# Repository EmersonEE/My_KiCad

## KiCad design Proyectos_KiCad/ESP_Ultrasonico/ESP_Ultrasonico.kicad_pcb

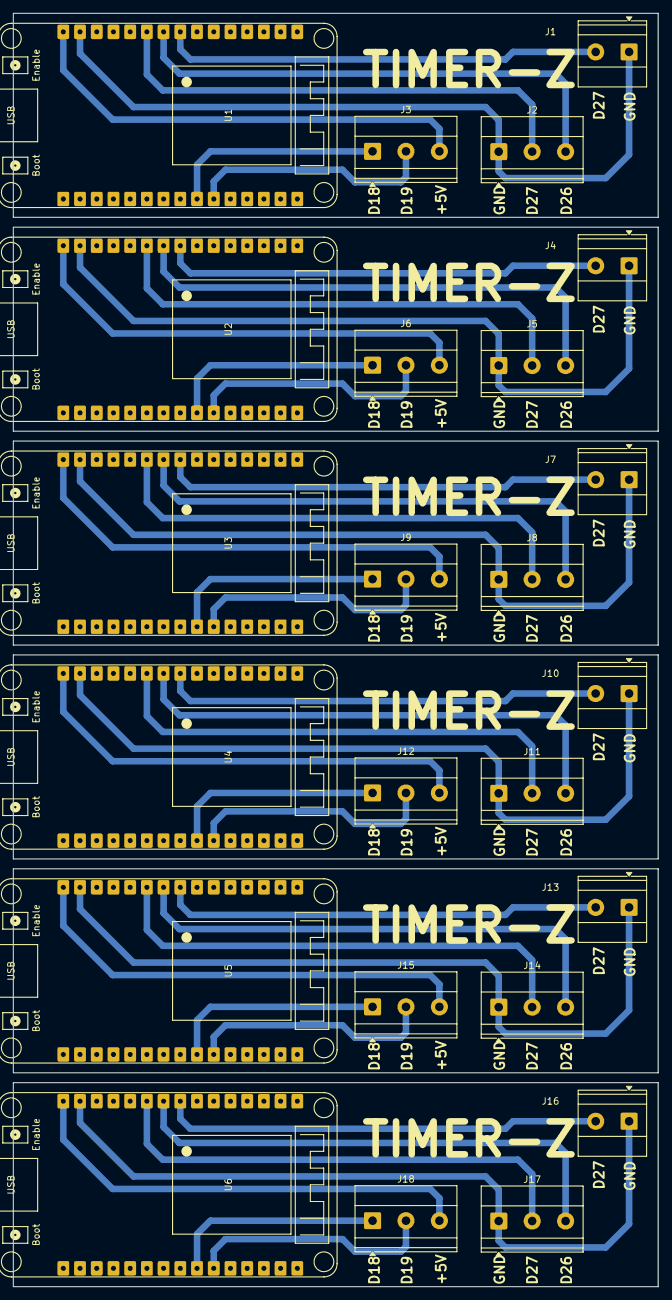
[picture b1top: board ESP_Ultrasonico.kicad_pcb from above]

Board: 2 copper layers, 98.0 x 193.5 mm, 24 parts (0 on the bottom side), 7 nets.

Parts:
J1, J4, J7, J10, J13, J16: Screw_Terminal_01x02; TerminalBlock_Phoenix_MKDS-1,5-2-5.08_1x02_P5.08mm_Horizont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
J2, J3, J5, J6, J8, J9, J11, J12, J14, J15, J17, J18: Screw_Terminal_01x03; TerminalBlock_Phoenix_MKDS-1,5-3-5.08_1x03_P5.08mm_Horizont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
U1, U2, U3, U4, U5, U6: ESP32_DevKit_V1_DOIT; ESP32_DEVKIT_V1_E32

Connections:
5V: J3.3, J6.3, J9.3, J12.3, J15.3, J18.3, U1.15 (VIN), U2.15 (VIN), U3.15 (VIN), U4.15 (VIN), U5.15 (VIN), U6.15 (VIN)
/CLK/GPIO18/D18: J3.1, J6.1, J9.1, J12.1, J15.1, J18.1, U1.24 (CLK/GPIO18/D18), U2.24 (CLK/GPIO18/D18), U3.24 (CLK/GPIO18/D18), U4.24 (CLK/GPIO18/D18), U5.24 (CLK/GPIO18/D18), U6.24 (CLK/GPIO18/D18)
/D25/GPIO25/ADC2/DAC1: J1.2, J4.2, J7.2, J10.2, J13.2, J16.2, U1.8 (D25/GPIO25/ADC2/DAC1), U2.8 (D25/GPIO25/ADC2/DAC1), U3.8 (D25/GPIO25/ADC2/DAC1), U4.8 (D25/GPIO25/ADC2/DAC1), U5.8 (D25/GPIO25/ADC2/DAC1), U6.8 (D25/GPIO25/ADC2/DAC1)
/D26/GPIO26/ADC2/DAC2: J2.3, J5.3, J8.3, J11.3, J14.3, J17.3, U1.9 (D26/GPIO26/ADC2/DAC2), U2.9 (D26/GPIO26/ADC2/DAC2), U3.9 (D26/GPIO26/ADC2/DAC2), U4.9 (D26/GPIO26/ADC2/DAC2), U5.9 (D26/GPIO26/ADC2/DAC2), U6.9 (D26/GPIO26/ADC2/DAC2)
/D27/GPIO27/ADC2/TOUCH7: J2.2, J5.2, J8.2, J11.2, J14.2, J17.2, U1.10 (D27/GPIO27/ADC2/TOUCH7), U2.10 (D27/GPIO27/ADC2/TOUCH7), U3.10 (D27/GPIO27/ADC2/TOUCH7), U4.10 (D27/GPIO27/ADC2/TOUCH7), U5.10 (D27/GPIO27/ADC2/TOUCH7), U6.10 (D27/GPIO27/ADC2/TOUCH7)
/MISO/GPIO19/D19: J3.2, J6.2, J9.2, J12.2, J15.2, J18.2, U1.25 (MISO/GPIO19/D19), U2.25 (MISO/GPIO19/D19), U3.25 (MISO/GPIO19/D19), U4.25 (MISO/GPIO19/D19), U5.25 (MISO/GPIO19/D19), U6.25 (MISO/GPIO19/D19)
GND: J1.1, J2.1, J4.1, J5.1, J7.1, J8.1, J10.1, J11.1, J13.1, J14.1, J16.1, J17.1, U1.14 (GND), U2.14 (GND), U3.14 (GND), U4.14 (GND), U5.14 (GND), U6.14 (GND)

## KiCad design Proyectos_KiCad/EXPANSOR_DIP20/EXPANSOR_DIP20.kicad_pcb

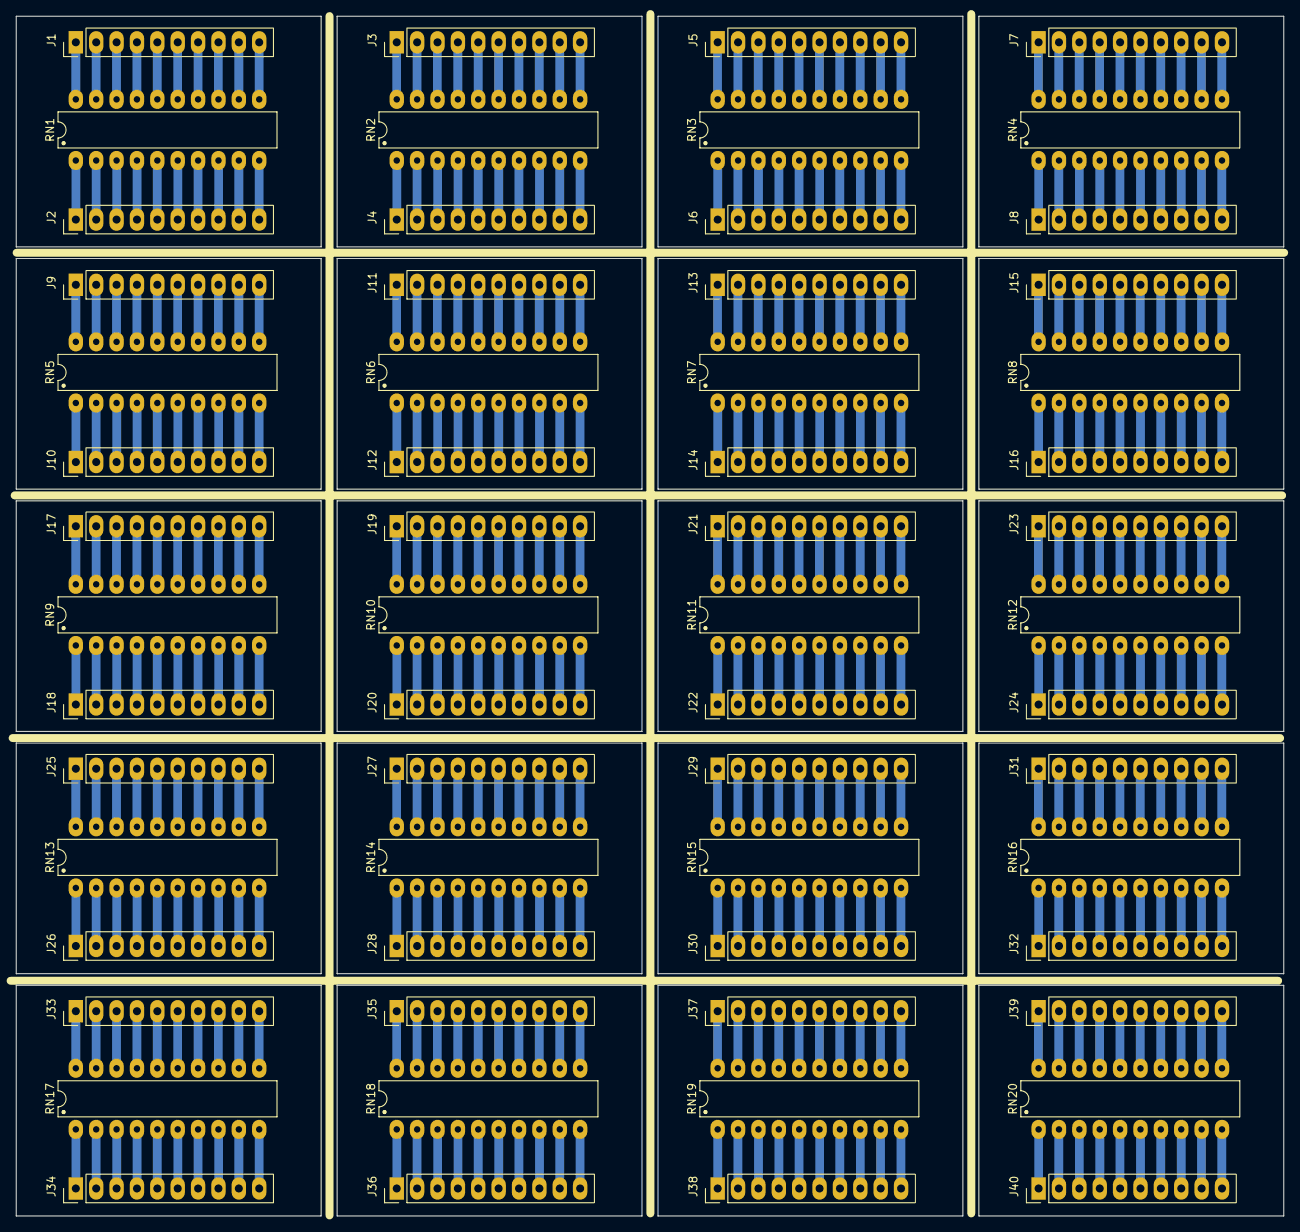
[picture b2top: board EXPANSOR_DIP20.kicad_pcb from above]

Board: 2 copper layers, 158.0 x 149.5 mm, 60 parts (0 on the bottom side), 20 nets.

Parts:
J1, J2, J3, J4, J5, J6, J7, J8, J9, J10, J11, J12, J13, J14, J15, J16, J17, J18, J19, J20, J21, J22, J23, J24, J25, J26, J27, J28, J29, J30, J31, J32, J33, J34, J35, J36, J37, J38, J39, J40: Conn_01x10; PinHeader_1x10_P2.54mm_Vertical
RN1, RN2, RN3, RN4, RN5, RN6, RN7, RN8, RN9, RN10, RN11, RN12, RN13, RN14, RN15, RN16, RN17, RN18, RN19, RN20: R_Pack_DIP-20; DIP-20_W7.62mm_LongPads

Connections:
unnamed: J1.1, J3.1, J5.1, J7.1, J9.1, J11.1, J13.1, J15.1, J17.1, J19.1, J21.1, J23.1, J25.1, J27.1, J29.1, J31.1, J33.1, J35.1, J37.1, J39.1, RN1.20 (R1.2), RN2.20 (R1.2), RN3.20 (R1.2), RN4.20 (R1.2), RN5.20 (R1.2), RN6.20 (R1.2), RN7.20 (R1.2), RN8.20 (R1.2), RN9.20 (R1.2), RN10.20 (R1.2), RN11.20 (R1.2), RN12.20 (R1.2), RN13.20 (R1.2), RN14.20 (R1.2), RN15.20 (R1.2), RN16.20 (R1.2), RN17.20 (R1.2), RN18.20 (R1.2), RN19.20 (R1.2), RN20.20 (R1.2)
unnamed: J1.2, J3.2, J5.2, J7.2, J9.2, J11.2, J13.2, J15.2, J17.2, J19.2, J21.2, J23.2, J25.2, J27.2, J29.2, J31.2, J33.2, J35.2, J37.2, J39.2, RN1.19 (R2.2), RN2.19 (R2.2), RN3.19 (R2.2), RN4.19 (R2.2), RN5.19 (R2.2), RN6.19 (R2.2), RN7.19 (R2.2), RN8.19 (R2.2), RN9.19 (R2.2), RN10.19 (R2.2), RN11.19 (R2.2), RN12.19 (R2.2), RN13.19 (R2.2), RN14.19 (R2.2), RN15.19 (R2.2), RN16.19 (R2.2), RN17.19 (R2.2), RN18.19 (R2.2), RN19.19 (R2.2), RN20.19 (R2.2)
unnamed: J1.3, J3.3, J5.3, J7.3, J9.3, J11.3, J13.3, J15.3, J17.3, J19.3, J21.3, J23.3, J25.3, J27.3, J29.3, J31.3, J33.3, J35.3, J37.3, J39.3, RN1.18 (R3.2), RN2.18 (R3.2), RN3.18 (R3.2), RN4.18 (R3.2), RN5.18 (R3.2), RN6.18 (R3.2), RN7.18 (R3.2), RN8.18 (R3.2), RN9.18 (R3.2), RN10.18 (R3.2), RN11.18 (R3.2), RN12.18 (R3.2), RN13.18 (R3.2), RN14.18 (R3.2), RN15.18 (R3.2), RN16.18 (R3.2), RN17.18 (R3.2), RN18.18 (R3.2), RN19.18 (R3.2), RN20.18 (R3.2)
unnamed: J1.4, J3.4, J5.4, J7.4, J9.4, J11.4, J13.4, J15.4, J17.4, J19.4, J21.4, J23.4, J25.4, J27.4, J29.4, J31.4, J33.4, J35.4, J37.4, J39.4, RN1.17 (R4.2), RN2.17 (R4.2), RN3.17 (R4.2), RN4.17 (R4.2), RN5.17 (R4.2), RN6.17 (R4.2), RN7.17 (R4.2), RN8.17 (R4.2), RN9.17 (R4.2), RN10.17 (R4.2), RN11.17 (R4.2), RN12.17 (R4.2), RN13.17 (R4.2), RN14.17 (R4.2), RN15.17 (R4.2), RN16.17 (R4.2), RN17.17 (R4.2), RN18.17 (R4.2), RN19.17 (R4.2), RN20.17 (R4.2)
unnamed: J1.5, J3.5, J5.5, J7.5, J9.5, J11.5, J13.5, J15.5, J17.5, J19.5, J21.5, J23.5, J25.5, J27.5, J29.5, J31.5, J33.5, J35.5, J37.5, J39.5, RN1.16 (R5.2), RN2.16 (R5.2), RN3.16 (R5.2), RN4.16 (R5.2), RN5.16 (R5.2), RN6.16 (R5.2), RN7.16 (R5.2), RN8.16 (R5.2), RN9.16 (R5.2), RN10.16 (R5.2), RN11.16 (R5.2), RN12.16 (R5.2), RN13.16 (R5.2), RN14.16 (R5.2), RN15.16 (R5.2), RN16.16 (R5.2), RN17.16 (R5.2), RN18.16 (R5.2), RN19.16 (R5.2), RN20.16 (R5.2)
unnamed: J1.6, J3.6, J5.6, J7.6, J9.6, J11.6, J13.6, J15.6, J17.6, J19.6, J21.6, J23.6, J25.6, J27.6, J29.6, J31.6, J33.6, J35.6, J37.6, J39.6, RN1.15 (R6.2), RN2.15 (R6.2), RN3.15 (R6.2), RN4.15 (R6.2), RN5.15 (R6.2), RN6.15 (R6.2), RN7.15 (R6.2), RN8.15 (R6.2), RN9.15 (R6.2), RN10.15 (R6.2), RN11.15 (R6.2), RN12.15 (R6.2), RN13.15 (R6.2), RN14.15 (R6.2), RN15.15 (R6.2), RN16.15 (R6.2), RN17.15 (R6.2), RN18.15 (R6.2), RN19.15 (R6.2), RN20.15 (R6.2)
unnamed: J1.7, J3.7, J5.7, J7.7, J9.7, J11.7, J13.7, J15.7, J17.7, J19.7, J21.7, J23.7, J25.7, J27.7, J29.7, J31.7, J33.7, J35.7, J37.7, J39.7, RN1.14 (R7.2), RN2.14 (R7.2), RN3.14 (R7.2), RN4.14 (R7.2), RN5.14 (R7.2), RN6.14 (R7.2), RN7.14 (R7.2), RN8.14 (R7.2), RN9.14 (R7.2), RN10.14 (R7.2), RN11.14 (R7.2), RN12.14 (R7.2), RN13.14 (R7.2), RN14.14 (R7.2), RN15.14 (R7.2), RN16.14 (R7.2), RN17.14 (R7.2), RN18.14 (R7.2), RN19.14 (R7.2), RN20.14 (R7.2)
unnamed: J1.8, J3.8, J5.8, J7.8, J9.8, J11.8, J13.8, J15.8, J17.8, J19.8, J21.8, J23.8, J25.8, J27.8, J29.8, J31.8, J33.8, J35.8, J37.8, J39.8, RN1.13 (R8.2), RN2.13 (R8.2), RN3.13 (R8.2), RN4.13 (R8.2), RN5.13 (R8.2), RN6.13 (R8.2), RN7.13 (R8.2), RN8.13 (R8.2), RN9.13 (R8.2), RN10.13 (R8.2), RN11.13 (R8.2), RN12.13 (R8.2), RN13.13 (R8.2), RN14.13 (R8.2), RN15.13 (R8.2), RN16.13 (R8.2), RN17.13 (R8.2), RN18.13 (R8.2), RN19.13 (R8.2), RN20.13 (R8.2)
unnamed: J1.9, J3.9, J5.9, J7.9, J9.9, J11.9, J13.9, J15.9, J17.9, J19.9, J21.9, J23.9, J25.9, J27.9, J29.9, J31.9, J33.9, J35.9, J37.9, J39.9, RN1.12 (R9.2), RN2.12 (R9.2), RN3.12 (R9.2), RN4.12 (R9.2), RN5.12 (R9.2), RN6.12 (R9.2), RN7.12 (R9.2), RN8.12 (R9.2), RN9.12 (R9.2), RN10.12 (R9.2), RN11.12 (R9.2), RN12.12 (R9.2), RN13.12 (R9.2), RN14.12 (R9.2), RN15.12 (R9.2), RN16.12 (R9.2), RN17.12 (R9.2), RN18.12 (R9.2), RN19.12 (R9.2), RN20.12 (R9.2)
unnamed: J1.10, J3.10, J5.10, J7.10, J9.10, J11.10, J13.10, J15.10, J17.10, J19.10, J21.10, J23.10, J25.10, J27.10, J29.10, J31.10, J33.10, J35.10, J37.10, J39.10, RN1.11 (R10.2), RN2.11 (R10.2), RN3.11 (R10.2), RN4.11 (R10.2), RN5.11 (R10.2), RN6.11 (R10.2), RN7.11 (R10.2), RN8.11 (R10.2), RN9.11 (R10.2), RN10.11 (R10.2), RN11.11 (R10.2), RN12.11 (R10.2), RN13.11 (R10.2), RN14.11 (R10.2), RN15.11 (R10.2), RN16.11 (R10.2), RN17.11 (R10.2), RN18.11 (R10.2), RN19.11 (R10.2), RN20.11 (R10.2)
unnamed: J2.1, J4.1, J6.1, J8.1, J10.1, J12.1, J14.1, J16.1, J18.1, J20.1, J22.1, J24.1, J26.1, J28.1, J30.1, J32.1, J34.1, J36.1, J38.1, J40.1, RN1.1 (R1.1), RN2.1 (R1.1), RN3.1 (R1.1), RN4.1 (R1.1), RN5.1 (R1.1), RN6.1 (R1.1), RN7.1 (R1.1), RN8.1 (R1.1), RN9.1 (R1.1), RN10.1 (R1.1), RN11.1 (R1.1), RN12.1 (R1.1), RN13.1 (R1.1), RN14.1 (R1.1), RN15.1 (R1.1), RN16.1 (R1.1), RN17.1 (R1.1), RN18.1 (R1.1), RN19.1 (R1.1), RN20.1 (R1.1)
unnamed: J2.2, J4.2, J6.2, J8.2, J10.2, J12.2, J14.2, J16.2, J18.2, J20.2, J22.2, J24.2, J26.2, J28.2, J30.2, J32.2, J34.2, J36.2, J38.2, J40.2, RN1.2 (R2.1), RN2.2 (R2.1), RN3.2 (R2.1), RN4.2 (R2.1), RN5.2 (R2.1), RN6.2 (R2.1), RN7.2 (R2.1), RN8.2 (R2.1), RN9.2 (R2.1), RN10.2 (R2.1), RN11.2 (R2.1), RN12.2 (R2.1), RN13.2 (R2.1), RN14.2 (R2.1), RN15.2 (R2.1), RN16.2 (R2.1), RN17.2 (R2.1), RN18.2 (R2.1), RN19.2 (R2.1), RN20.2 (R2.1)
unnamed: J2.3, J4.3, J6.3, J8.3, J10.3, J12.3, J14.3, J16.3, J18.3, J20.3, J22.3, J24.3, J26.3, J28.3, J30.3, J32.3, J34.3, J36.3, J38.3, J40.3, RN1.3 (R3.1), RN2.3 (R3.1), RN3.3 (R3.1), RN4.3 (R3.1), RN5.3 (R3.1), RN6.3 (R3.1), RN7.3 (R3.1), RN8.3 (R3.1), RN9.3 (R3.1), RN10.3 (R3.1), RN11.3 (R3.1), RN12.3 (R3.1), RN13.3 (R3.1), RN14.3 (R3.1), RN15.3 (R3.1), RN16.3 (R3.1), RN17.3 (R3.1), RN18.3 (R3.1), RN19.3 (R3.1), RN20.3 (R3.1)
unnamed: J2.4, J4.4, J6.4, J8.4, J10.4, J12.4, J14.4, J16.4, J18.4, J20.4, J22.4, J24.4, J26.4, J28.4, J30.4, J32.4, J34.4, J36.4, J38.4, J40.4, RN1.4 (R4.1), RN2.4 (R4.1), RN3.4 (R4.1), RN4.4 (R4.1), RN5.4 (R4.1), RN6.4 (R4.1), RN7.4 (R4.1), RN8.4 (R4.1), RN9.4 (R4.1), RN10.4 (R4.1), RN11.4 (R4.1), RN12.4 (R4.1), RN13.4 (R4.1), RN14.4 (R4.1), RN15.4 (R4.1), RN16.4 (R4.1), RN17.4 (R4.1), RN18.4 (R4.1), RN19.4 (R4.1), RN20.4 (R4.1)
unnamed: J2.5, J4.5, J6.5, J8.5, J10.5, J12.5, J14.5, J16.5, J18.5, J20.5, J22.5, J24.5, J26.5, J28.5, J30.5, J32.5, J34.5, J36.5, J38.5, J40.5, RN1.5 (R5.1), RN2.5 (R5.1), RN3.5 (R5.1), RN4.5 (R5.1), RN5.5 (R5.1), RN6.5 (R5.1), RN7.5 (R5.1), RN8.5 (R5.1), RN9.5 (R5.1), RN10.5 (R5.1), RN11.5 (R5.1), RN12.5 (R5.1), RN13.5 (R5.1), RN14.5 (R5.1), RN15.5 (R5.1), RN16.5 (R5.1), RN17.5 (R5.1), RN18.5 (R5.1), RN19.5 (R5.1), RN20.5 (R5.1)
unnamed: J2.6, J4.6, J6.6, J8.6, J10.6, J12.6, J14.6, J16.6, J18.6, J20.6, J22.6, J24.6, J26.6, J28.6, J30.6, J32.6, J34.6, J36.6, J38.6, J40.6, RN1.6 (R6.1), RN2.6 (R6.1), RN3.6 (R6.1), RN4.6 (R6.1), RN5.6 (R6.1), RN6.6 (R6.1), RN7.6 (R6.1), RN8.6 (R6.1), RN9.6 (R6.1), RN10.6 (R6.1), RN11.6 (R6.1), RN12.6 (R6.1), RN13.6 (R6.1), RN14.6 (R6.1), RN15.6 (R6.1), RN16.6 (R6.1), RN17.6 (R6.1), RN18.6 (R6.1), RN19.6 (R6.1), RN20.6 (R6.1)
unnamed: J2.7, J4.7, J6.7, J8.7, J10.7, J12.7, J14.7, J16.7, J18.7, J20.7, J22.7, J24.7, J26.7, J28.7, J30.7, J32.7, J34.7, J36.7, J38.7, J40.7, RN1.7 (R7.1), RN2.7 (R7.1), RN3.7 (R7.1), RN4.7 (R7.1), RN5.7 (R7.1), RN6.7 (R7.1), RN7.7 (R7.1), RN8.7 (R7.1), RN9.7 (R7.1), RN10.7 (R7.1), RN11.7 (R7.1), RN12.7 (R7.1), RN13.7 (R7.1), RN14.7 (R7.1), RN15.7 (R7.1), RN16.7 (R7.1), RN17.7 (R7.1), RN18.7 (R7.1), RN19.7 (R7.1), RN20.7 (R7.1)
unnamed: J2.8, J4.8, J6.8, J8.8, J10.8, J12.8, J14.8, J16.8, J18.8, J20.8, J22.8, J24.8, J26.8, J28.8, J30.8, J32.8, J34.8, J36.8, J38.8, J40.8, RN1.8 (R8.1), RN2.8 (R8.1), RN3.8 (R8.1), RN4.8 (R8.1), RN5.8 (R8.1), RN6.8 (R8.1), RN7.8 (R8.1), RN8.8 (R8.1), RN9.8 (R8.1), RN10.8 (R8.1), RN11.8 (R8.1), RN12.8 (R8.1), RN13.8 (R8.1), RN14.8 (R8.1), RN15.8 (R8.1), RN16.8 (R8.1), RN17.8 (R8.1), RN18.8 (R8.1), RN19.8 (R8.1), RN20.8 (R8.1)
unnamed: J2.9, J4.9, J6.9, J8.9, J10.9, J12.9, J14.9, J16.9, J18.9, J20.9, J22.9, J24.9, J26.9, J28.9, J30.9, J32.9, J34.9, J36.9, J38.9, J40.9, RN1.9 (R9.1), RN2.9 (R9.1), RN3.9 (R9.1), RN4.9 (R9.1), RN5.9 (R9.1), RN6.9 (R9.1), RN7.9 (R9.1), RN8.9 (R9.1), RN9.9 (R9.1), RN10.9 (R9.1), RN11.9 (R9.1), RN12.9 (R9.1), RN13.9 (R9.1), RN14.9 (R9.1), RN15.9 (R9.1), RN16.9 (R9.1), RN17.9 (R9.1), RN18.9 (R9.1), RN19.9 (R9.1), RN20.9 (R9.1)
unnamed: J2.10, J4.10, J6.10, J8.10, J10.10, J12.10, J14.10, J16.10, J18.10, J20.10, J22.10, J24.10, J26.10, J28.10, J30.10, J32.10, J34.10, J36.10, J38.10, J40.10, RN1.10 (R10.1), RN2.10 (R10.1), RN3.10 (R10.1), RN4.10 (R10.1), RN5.10 (R10.1), RN6.10 (R10.1), RN7.10 (R10.1), RN8.10 (R10.1), RN9.10 (R10.1), RN10.10 (R10.1), RN11.10 (R10.1), RN12.10 (R10.1), RN13.10 (R10.1), RN14.10 (R10.1), RN15.10 (R10.1), RN16.10 (R10.1), RN17.10 (R10.1), RN18.10 (R10.1), RN19.10 (R10.1), RN20.10 (R10.1)

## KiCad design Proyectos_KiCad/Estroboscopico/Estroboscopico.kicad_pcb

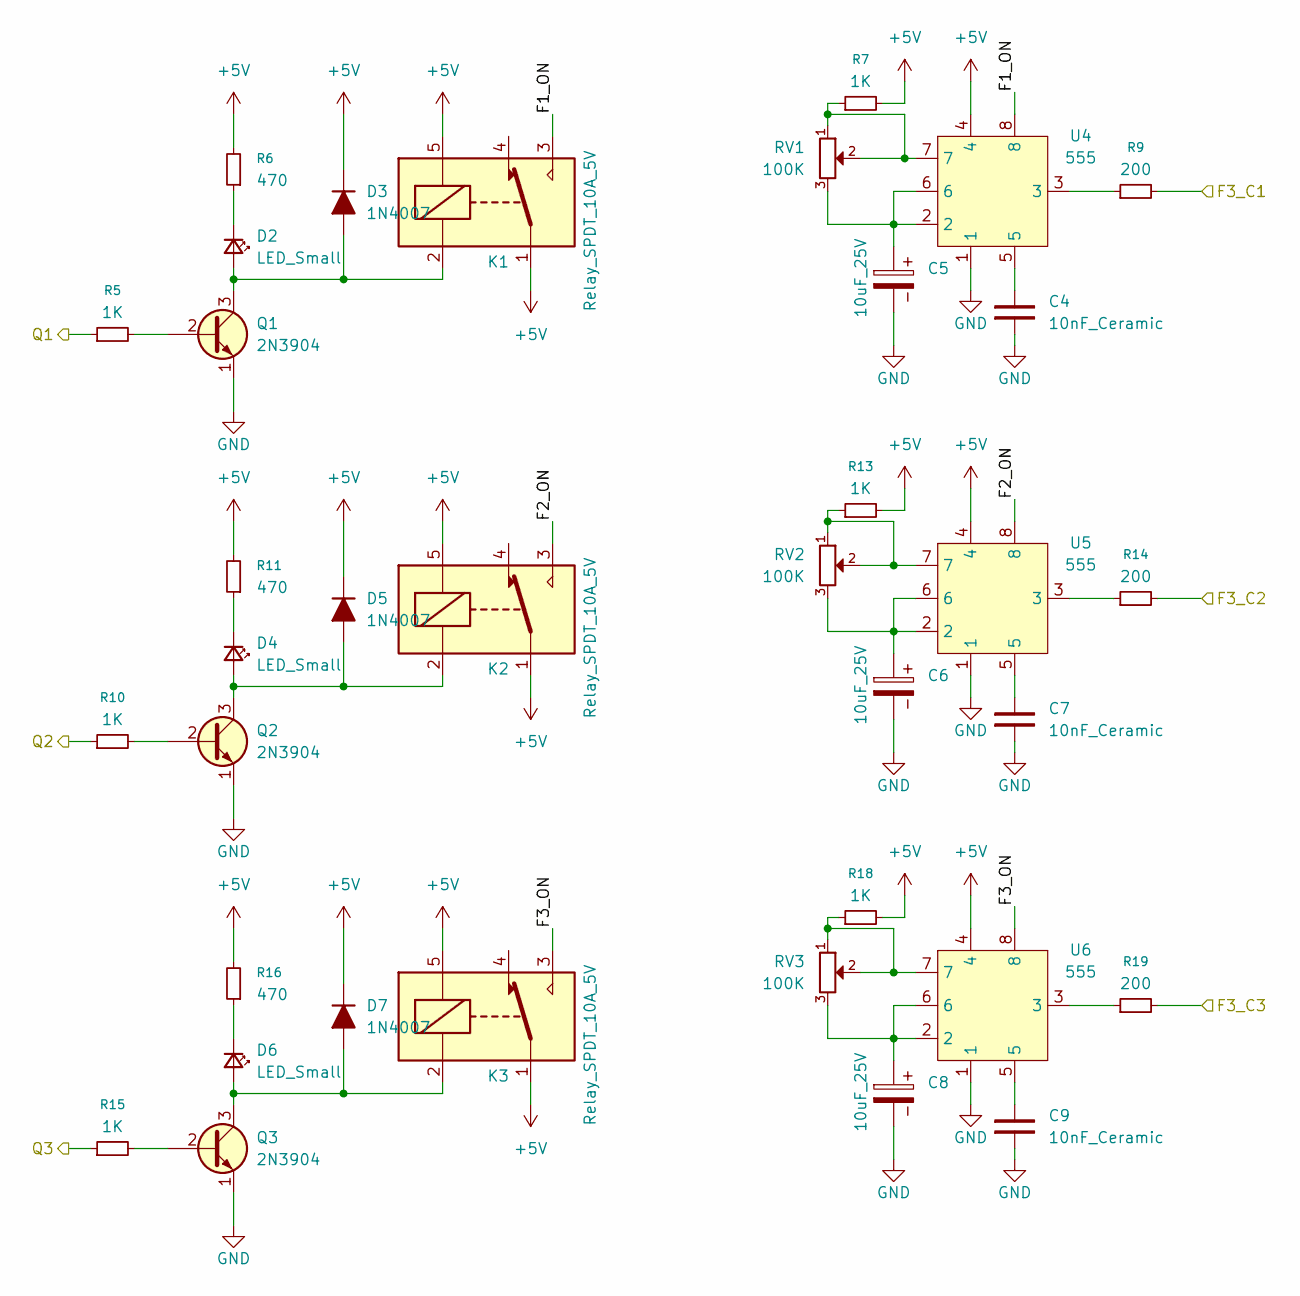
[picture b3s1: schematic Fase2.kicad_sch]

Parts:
C4, C7, C9: 10nF_Ceramic; C_Disc_D5.0mm_W2.5mm_P2.50mm
C5, C6, C8: 10uF_25V; CP_Radial_D6.3mm_P2.50mm
D2, D4, D6: LED_Small; LED_D5.0mm
D3, D5, D7: 1N4007; D_DO-41_SOD81_P7.62mm_Horizontal
K1, K2, K3: Relay_SPDT_10A_5V; Relay_SPDT_SANYOU_SRD_Series_Form_C
Q1, Q2, Q3: 2N3904; TO-92_Inline_Wide_EBC
R5, R7, R10, R13, R15, R18: 1K; R_Axial_DIN0204_L3.6mm_D1.6mm_P10.16mm_Horizontal
R6, R11, R16: 470; R_Axial_DIN0204_L3.6mm_D1.6mm_P10.16mm_Horizontal
R9, R14, R19: 200; R_Axial_DIN0204_L3.6mm_D1.6mm_P10.16mm_Horizontal
RV1, RV2, RV3: 100K; Potentiometer_Bourns_3266Y_Vertical
U4, U5, U6: 555; DIP-8_W7.62mm_Socket_LongPads

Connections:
+5V: D3.1 (K), D5.1 (K), D7.1 (K), K1.1, K1.5, K2.1, K2.5, K3.1, K3.5, R6.2, R7.2, R11.2, R13.2, R16.2, R18.2, U4.4, U5.4, U6.4; also elsewhere on the board
/Fas1/Q1: R5.1; also elsewhere on the board
/Fas1/Q2: R10.1; also elsewhere on the board
/Fas1/Q3: R15.1; also elsewhere on the board
/Fase2/F1_ON: K1.3, U4.8
/Fase2/F2_ON: K2.3, U5.8
/Fase2/F3_C1: R9.2; also elsewhere on the board
/Fase2/F3_C2: R14.2; also elsewhere on the board
/Fase2/F3_C3: R19.2; also elsewhere on the board
/Fase2/F3_ON: K3.3, U6.8
GND: C4.1, C5.2, C6.2, C7.1, C8.2, C9.1, Q1.1 (E), Q2.1 (E), Q3.1 (E), U4.1, U5.1, U6.1; also elsewhere on the board
unnamed: C4.2, U4.5
unnamed: C5.1, RV1.3, U4.2, U4.6
unnamed: C6.1, RV2.3, U5.2, U5.6
unnamed: C7.2, U5.5
unnamed: C8.1, RV3.3, U6.2, U6.6
unnamed: C9.2, U6.5
unnamed: D2.2 (A), D3.2 (A), K1.2, Q1.3 (C)
unnamed: D2.1 (K), R6.1
unnamed: D4.2 (A), D5.2 (A), K2.2, Q2.3 (C)
unnamed: D4.1 (K), R11.1
unnamed: D6.2 (A), D7.2 (A), K3.2, Q3.3 (C)
unnamed: D6.1 (K), R16.1
unnamed: Q1.2 (B), R5.2
unnamed: Q2.2 (B), R10.2
unnamed: Q3.2 (B), R15.2
unnamed: R7.1, RV1.1, RV1.2, U4.7
unnamed: R9.1, U4.3
unnamed: R13.1, RV2.1, RV2.2, U5.7
unnamed: R14.1, U5.3
unnamed: R18.1, RV3.1, RV3.2, U6.7
unnamed: R19.1, U6.3

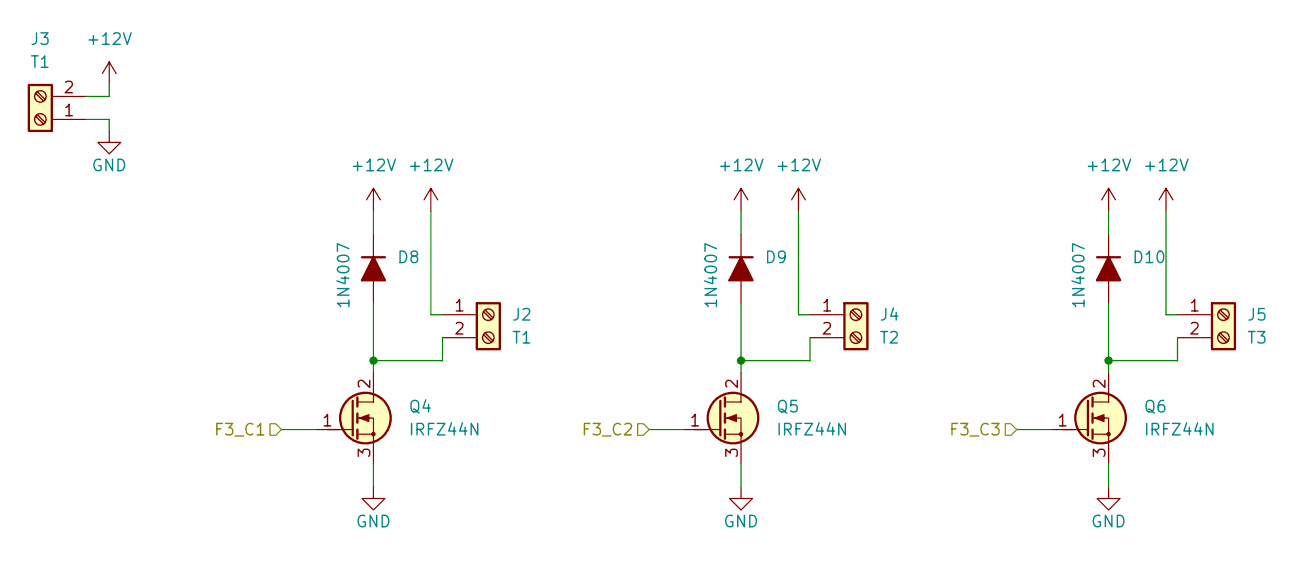
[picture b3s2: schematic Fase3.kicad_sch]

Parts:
D8, D9, D10: 1N4007; D_DO-41_SOD81_P7.62mm_Horizontal
J2, J3: T1; TerminalBlock_Phoenix_MKDS-1,5-2-5.08_1x02_P5.08mm_Horizont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
J4: T2; TerminalBlock_Phoenix_MKDS-1,5-2-5.08_1x02_P5.08mm_Horizont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
J5: T3; TerminalBlock_Phoenix_MKDS-1,5-2-5.08_1x02_P5.08mm_Horizont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
Q4, Q5, Q6: IRFZ44N; TO-220-3_Vertical_GDS

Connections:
+12V: D8.1 (K), D9.1 (K), D10.1 (K), J2.1, J3.2, J4.1, J5.1
/Fase2/F3_C1: Q4.1 (G); also elsewhere on the board
/Fase2/F3_C2: Q5.1 (G); also elsewhere on the board
/Fase2/F3_C3: Q6.1 (G); also elsewhere on the board
GND: J3.1, Q4.3 (S), Q5.3 (S), Q6.3 (S); also elsewhere on the board
unnamed: D8.2 (A), J2.2, Q4.2 (D)
unnamed: D9.2 (A), J4.2, Q5.2 (D)
unnamed: D10.2 (A), J5.2, Q6.2 (D)

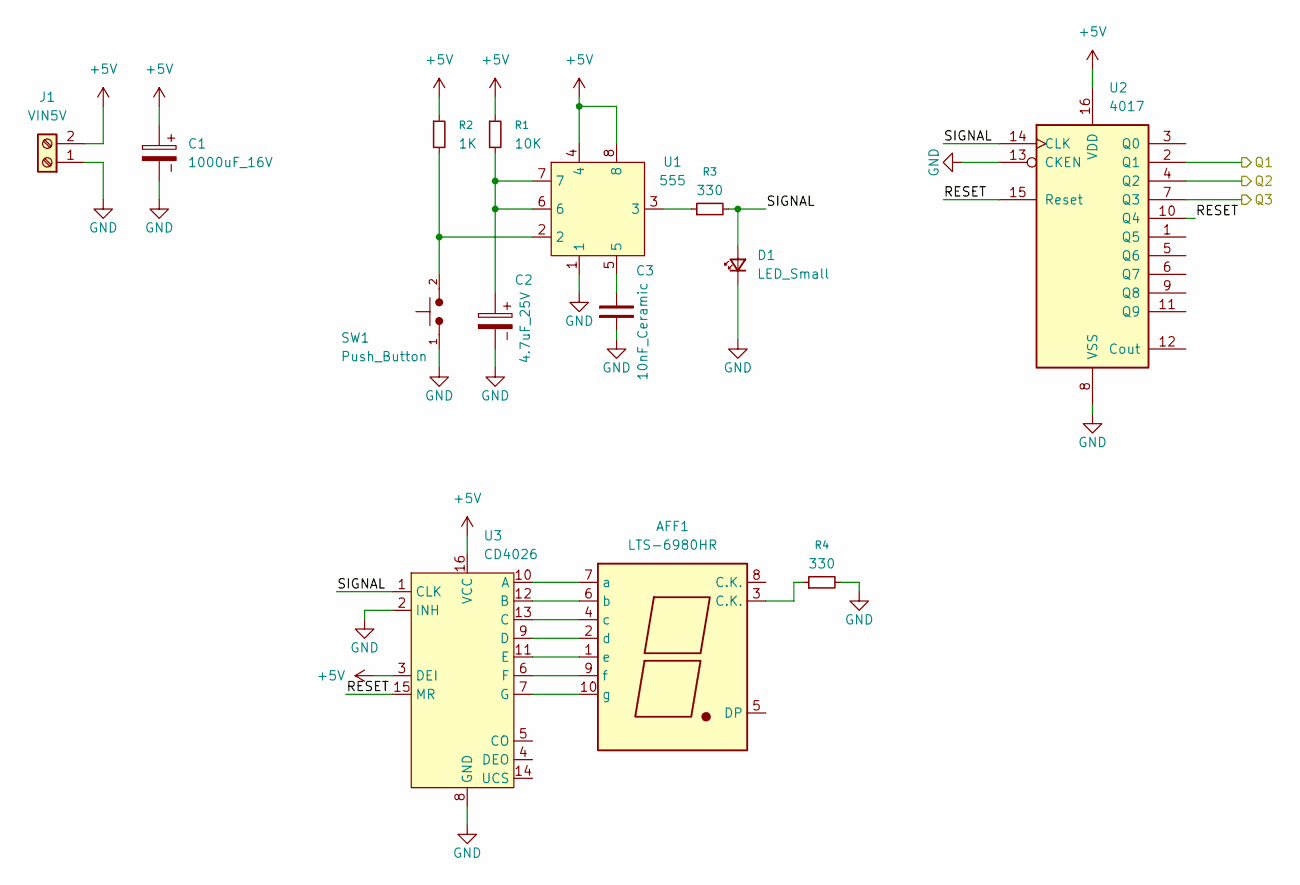
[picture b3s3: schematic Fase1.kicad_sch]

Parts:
AFF1: LTS-6980HR; 7SegmentLED_LTS6760_LTS6780
C1: 1000uF_16V; CP_Radial_D10.0mm_P5.00mm
C2: 4.7uF_25V; CP_Radial_D4.0mm_P1.50mm
C3: 10nF_Ceramic; C_Disc_D5.0mm_W2.5mm_P2.50mm
D1: LED_Small; LED_D5.0mm
J1: VIN5V; TerminalBlock_Phoenix_MKDS-1,5-2-5.08_1x02_P5.08mm_Horizont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
R1: 10K; R_Axial_DIN0204_L3.6mm_D1.6mm_P10.16mm_Horizontal
R2: 1K; R_Axial_DIN0204_L3.6mm_D1.6mm_P10.16mm_Horizontal
R3, R4: 330; R_Axial_DIN0204_L3.6mm_D1.6mm_P10.16mm_Horizontal
SW1: Push_Button; SW_PUSH_6mm
U1: 555; DIP-8_W7.62mm_Socket_LongPads
U2: 4017; DIP-16_W7.62mm_LongPads
U3: CD4026; DIP-16_W7.62mm_LongPads

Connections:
+5V: C1.1, J1.2, R1.1, R2.1, U1.4, U1.8, U2.16 (VDD), U3.3 (DEI), U3.16 (VCC); also elsewhere on the board
/Fas1/Q1: U2.2 (Q1); also elsewhere on the board
/Fas1/Q2: U2.4 (Q2); also elsewhere on the board
/Fas1/Q3: U2.7 (Q3); also elsewhere on the board
/Fas1/RESET: U2.10 (Q4), U2.15 (Reset), U3.15 (MR)
/Fas1/SIGNAL: D1.2 (A), R3.2, U2.14 (CLK), U3.1 (CLK)
GND: C1.2, C2.2, C3.1, D1.1 (K), J1.1, R4.2, SW1.1, U1.1, U2.8 (VSS), U2.13 (CKEN), U3.2 (INH), U3.8 (GND); also elsewhere on the board
unnamed: AFF1.3 (C.K.), R4.1
unnamed: AFF1.7 (a), U3.10 (A)
unnamed: AFF1.6 (b), U3.12 (B)
unnamed: AFF1.4 (c), U3.13 (C)
unnamed: AFF1.2 (d), U3.9 (D)
unnamed: AFF1.1 (e), U3.11 (E)
unnamed: AFF1.9 (f), U3.6 (F)
unnamed: AFF1.10 (g), U3.7 (G)
unnamed: C2.1, R1.2, U1.6, U1.7
unnamed: C3.2, U1.5
unnamed: R2.2, SW1.2, U1.2
unnamed: R3.1, U1.3

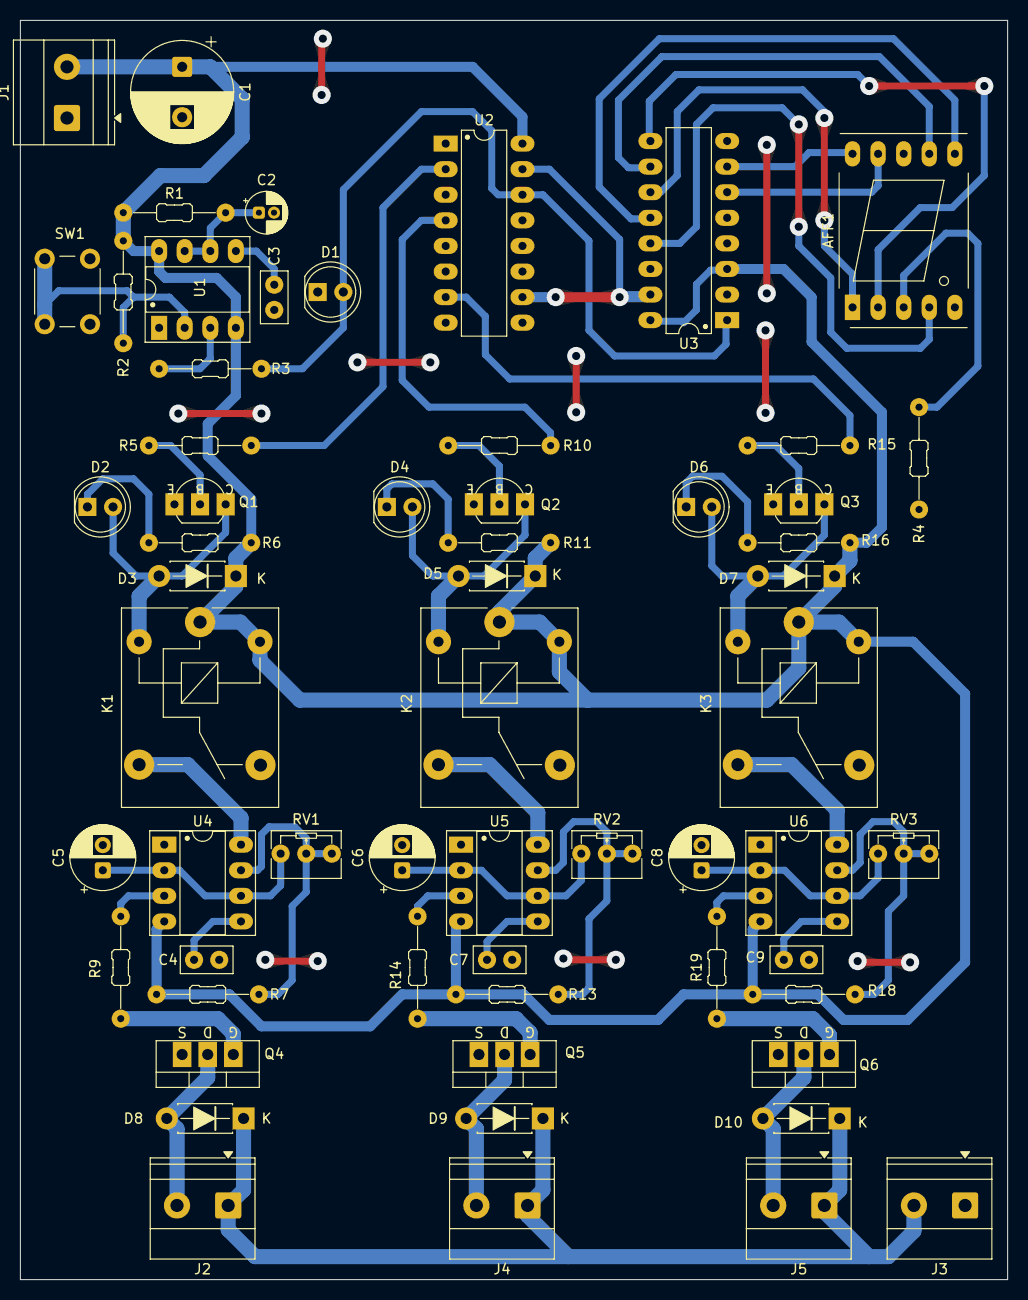
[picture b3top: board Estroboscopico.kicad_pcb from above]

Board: 2 copper layers, 98.0 x 125.0 mm, 60 parts (0 on the bottom side), 50 nets.

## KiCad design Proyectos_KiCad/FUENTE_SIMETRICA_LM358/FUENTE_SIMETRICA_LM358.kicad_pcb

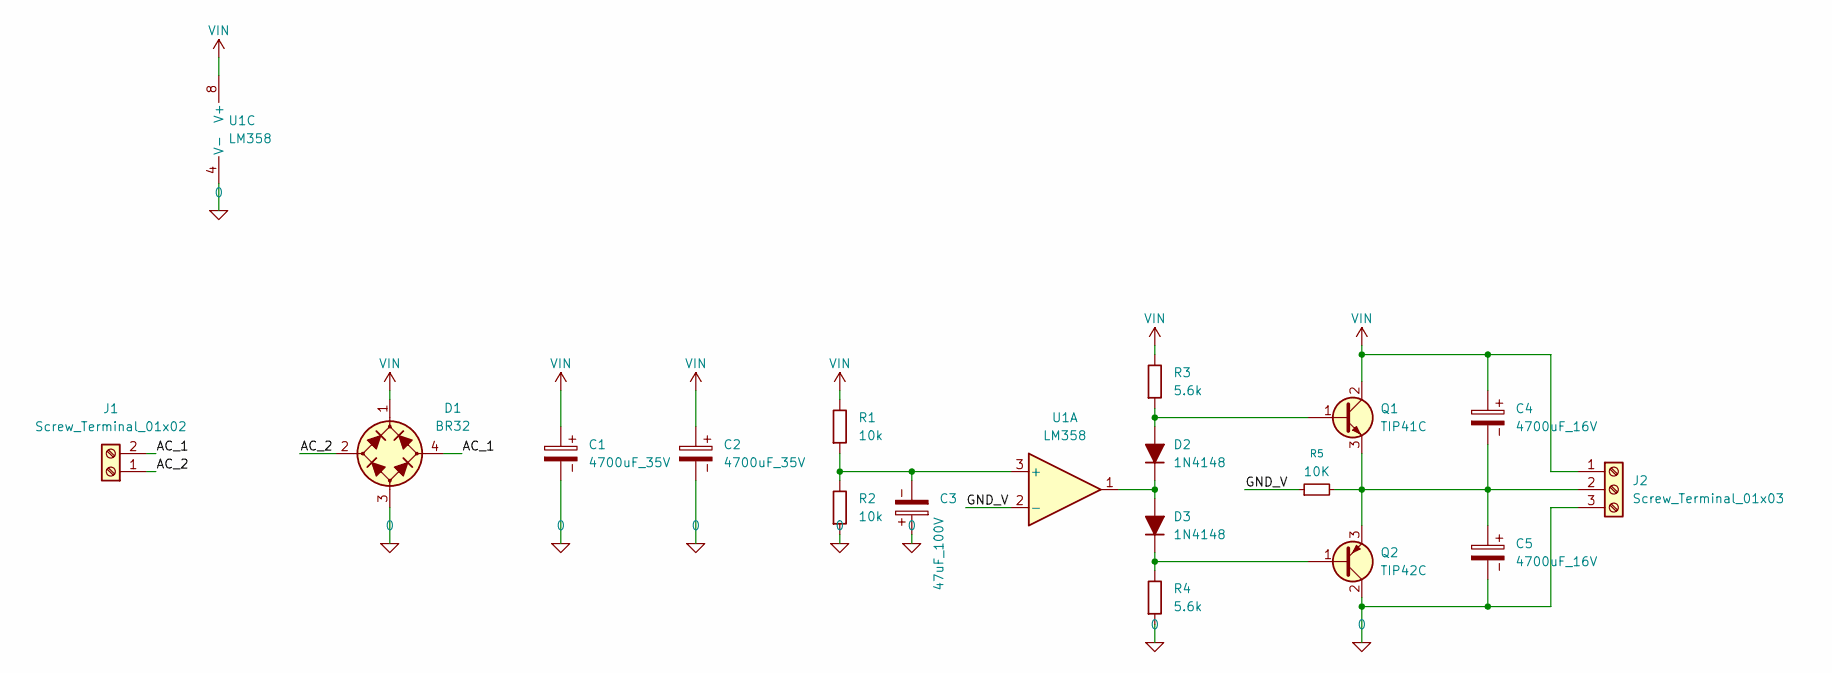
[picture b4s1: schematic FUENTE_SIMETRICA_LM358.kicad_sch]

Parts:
C1, C2: 4700uF_35V; CP_Radial_D18.0mm_P7.50mm
C3: 47uF_100V; CP_Radial_D10.0mm_P5.00mm
C4, C5: 4700uF_16V; CP_Radial_D14.0mm_P5.00mm
D1: BR32; Diode_Bridge_15.1x15.1x6.3mm_P10.9mm
D2, D3: 1N4148; D_DO-35_SOD27_P7.62mm_Horizontal
J1: Screw_Terminal_01x02; TerminalBlock_Phoenix_MKDS-1,5-2-5.08_1x02_P5.08mm_Horizont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
J2: Screw_Terminal_01x03; TerminalBlock_Phoenix_MKDS-1,5-3-5.08_1x03_P5.08mm_Horizont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
Q1: TIP41C; TO-220-3_Vertical_BCE
Q2: TIP42C; TO-220-3_Vertical_BCE
R1, R2: 10k; R_Axial_DIN0207_L6.3mm_D2.5mm_P15.24mm_Horizontal
R3, R4: 5.6k; R_Axial_DIN0207_L6.3mm_D2.5mm_P15.24mm_Horizontal
R5: 10K
U1: LM358; DIP-8_W7.62mm_LongPads

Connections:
0: C1.2, C2.2, C3.1, C5.2, D1.3 (-), J2.3, Q2.2 (C), R2.1, R4.1, U1.4 (V-)
/AC_1: D1.4 (2), J1.2
/AC_2: D1.2 (1), J1.1
/GND_V: R5.1, U1.2 (-)
unnamed: D2.2 (A), Q1.1 (B), R3.1
unnamed: D2.1 (K), D3.2 (A), U1.1
unnamed: D3.1 (K), Q2.1 (B), R4.2
unnamed: C4.2, C5.1, J2.2, Q1.3 (E), Q2.3 (E), R5.2
unnamed: C3.2, R1.1, R2.2, U1.3 (+)
VIN: C1.1, C2.1, C4.1, D1.1 (+), J2.1, Q1.2 (C), R1.2, R3.2, U1.8 (V+)

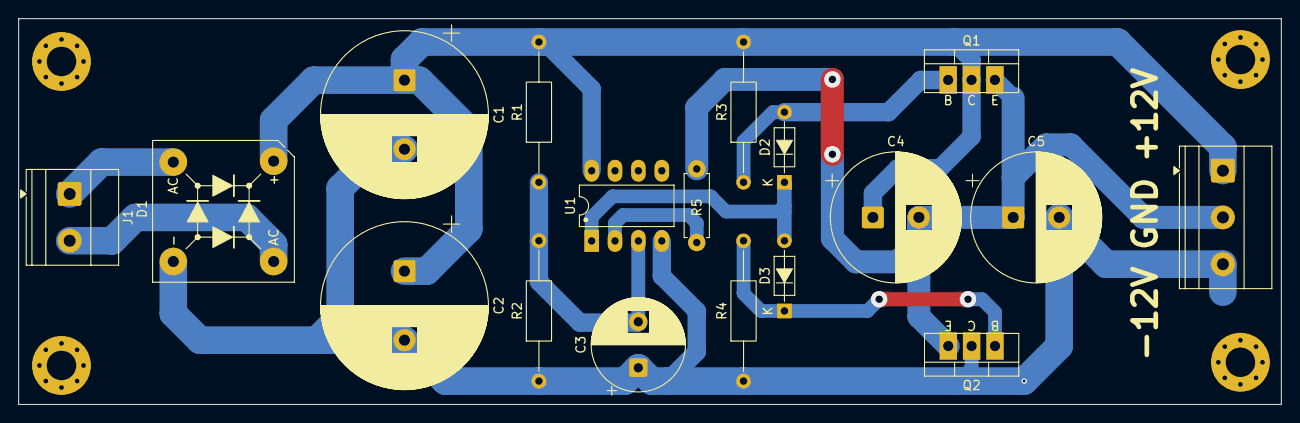
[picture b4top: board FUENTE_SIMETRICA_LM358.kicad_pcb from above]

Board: 2 copper layers, 137.2 x 41.9 mm, 18 parts (0 on the bottom side), 10 nets.

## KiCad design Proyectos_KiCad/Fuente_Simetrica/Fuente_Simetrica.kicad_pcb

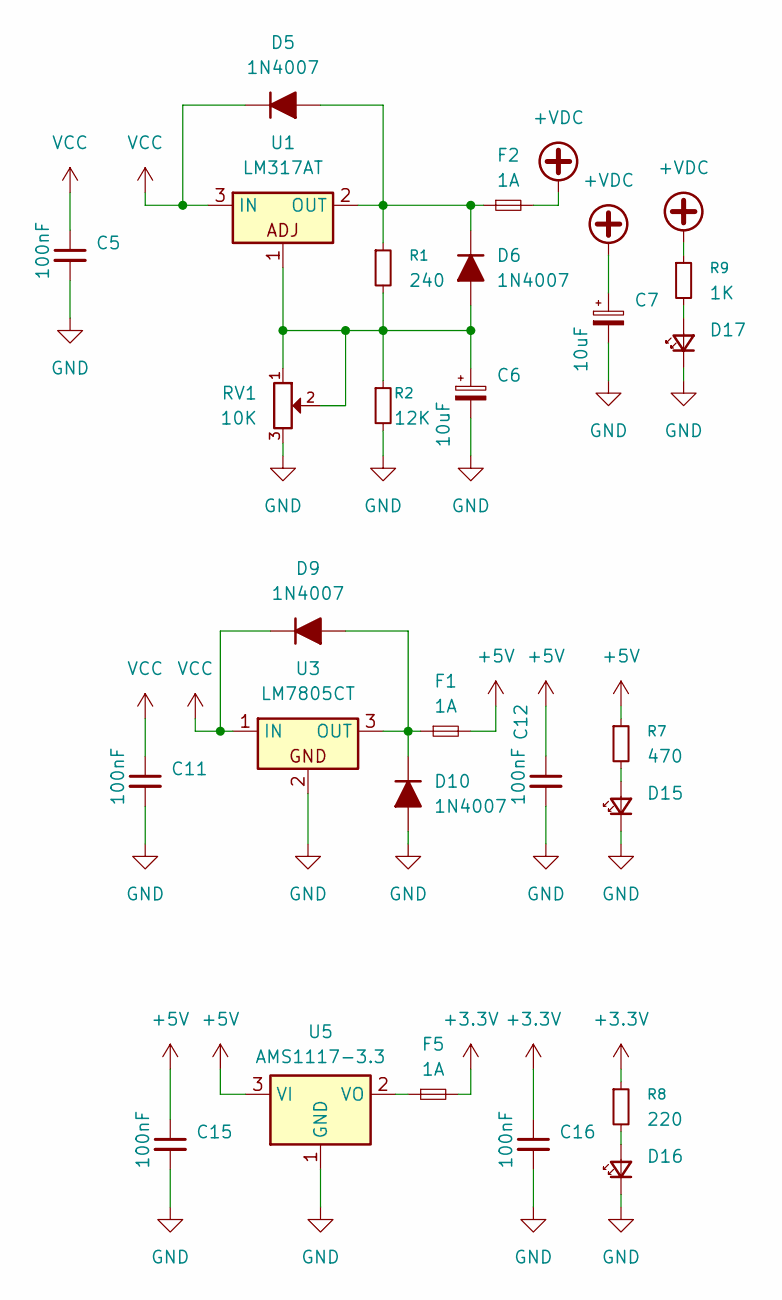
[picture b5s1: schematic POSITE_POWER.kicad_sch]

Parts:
C5, C11, C12, C15, C16: 100nF; C_Disc_D3.0mm_W2.0mm_P2.50mm
C6, C7: 10uF; CP_Radial_D5.0mm_P2.50mm
D5, D9: 1N4007; D_SMA
D6, D10: 1N4007; D_DO-41_SOD81_P7.62mm_Horizontal
D15, D16, D17: LED_D5.0mm
F1, F2, F5: 1A; Fuse_5x22mm
R1: 240; 220
R2: 12K; 220
R7: 470
R8: 220
R9: 1K
RV1: 10K; Molex_KK-254_AE-6410-03A_1x03_P2.54mm_Vertical
U1: LM317AT; TO-220-3_Vertical
U3: LM7805CT; TO-220-3_Vertical
U5: AMS1117-3.3; SOT-223-3_TabPin2

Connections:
+3.3V: C16.1, F5.2, R8.1; also elsewhere on the board
+5V: C12.1, C15.1, F1.2, R7.1, U5.3 (VI); also elsewhere on the board
+VDC: C7.1, F2.2, R9.1; also elsewhere on the board
GND: C5.2, C6.2, C7.2, C11.2, C12.2, C15.2, C16.2, D10.2 (A), D15.1 (K), D16.1 (K), D17.1 (K), R2.2, RV1.3, U3.2, U5.1 (GND); also elsewhere on the board
unnamed: D5.2 (A), D6.1 (K), F2.1, R1.1, U1.2 (OUT)
unnamed: C6.1, D6.2 (A), R1.2, R2.1, RV1.1, RV1.2, U1.1
unnamed: D9.2 (A), D10.1 (K), F1.1, U3.3 (OUT)
unnamed: D15.2 (A), R7.2
unnamed: D16.2 (A), R8.2
unnamed: D17.2 (A), R9.2
unnamed: F5.1, U5.2 (VO)
VCC: C5.1, C11.1, D5.1 (K), D9.1 (K), U1.3 (IN), U3.1 (IN); also elsewhere on the board
